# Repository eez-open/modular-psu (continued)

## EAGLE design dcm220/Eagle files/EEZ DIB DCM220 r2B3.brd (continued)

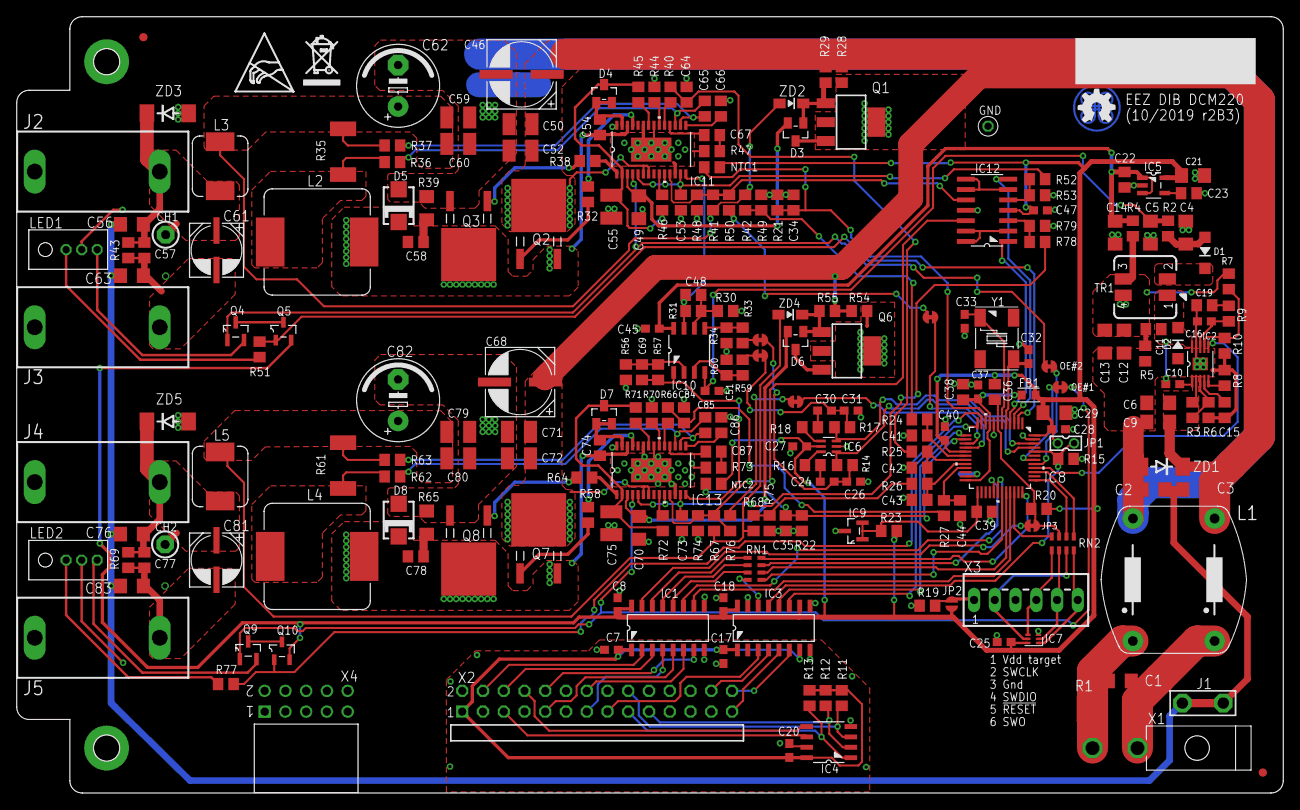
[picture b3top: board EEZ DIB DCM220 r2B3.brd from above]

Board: 2 copper layers, 155.0 x 95.0 mm, 248 parts (1 on the bottom side), 174 nets.

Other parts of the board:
EEZ_SIGNATURE: SIGNATURESMALL; SIGNATURE_5MM
U$2: RECYCLE_BIN1/8
U$4: ESD_SYMBOL

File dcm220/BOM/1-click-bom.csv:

References,Qty,Description,Manufacturer,MPN,Digikey,Mouser,RS,Newark,Farnell
"C1, C2, C3, C56, C63, C76, C83",7,10n/200V,,885342207005,311-4491-1-ND,603C1206KRX7RABB103,CC1206KRX7RABB103,,885342207005
C11,1,330p,,C0805C331J5GACTU,1276-1189-1-ND,80C0805C331J5G,0805N331J500CT,,C0805C331J5GACTU
"C12, C55, C75",3,22u,,MC1206X226M100CT,1276-1287-1-ND,963LMK316ABJ226MLT,LMK316ABJ226KL,,MC1206X226M100CT
"C15, C19, C23, C34, C35, C66, C86",7,10n,,VJ0805Y103JXXPW1BC,490-7194-1-ND,710885012207122,08055C103KAT2A,,VJ0805Y103JXXPW1BC
C16,1,33p,,MC0805N330J500CT,1276-1105-1-ND,C0805C330K5GACTU,C0805C330J5GACTU,,MC0805N330J500CT
"C32, C33",2,4p7,,MC0603N4R7C500CT,311-1740-1-ND,710885012006049,C0603C479C5GACTU,,MC0603N4R7C500CT
C36,1,1n,,VJ0805A102JXACW1BC,732-7858-1-ND,710885012007040,GRM2195C1H102JA01D,,VJ0805A102JXACW1BC
"C38, C53, C57, C73, C77",5,1u,,VJ0805Y105KXXTW1BC,587-1283-1-ND,603CC805MKX7R7BB105,C0805C105K4RACTU,,VJ0805Y105KXXTW1BC
"C39, C41, C42, C43, C44, C67, C87",7,4n7,,GRM2165C1H472JA01D,732-12255-1-ND,810C2012C0G1H472J1,C2012C0G1H472J060AA,,GRM2165C1H472JA01D
"C4, C5, C14, C29, C49, C70",6,4u7,,C3216X7R1E475K160AC,1276-2970-1-ND,963EMK316B7475MLT,C1206C475K3RACTU,,C3216X7R1E475K160AC
"C46, C68",2,EEEFK1H470,,EEEFK1H470P,PCE3815CT-ND,667EEEFK1H470P,EEEFK1H470P,,EEEFK1H470P
"C48, C69",2,100p,,C0805C101JAGACTU,399-15000-1-ND,80C0805C101K5G,CC0805JRNP09BN101,,C0805C101JAGACTU
"C50, C52, C71, C72",4,10u,,GRT31CR61H106KE01L,1276-6736-1-ND,810C3216X7R1HK160AC,UMK316BBJ106KLT,,GRT31CR61H106KE01L
"C54, C74",2,220n,,MC0805B224J250CT,1276-6477-1-ND,963EMK212B7224KGT,UMK212B7224KGT,,MC0805B224J250CT
"C59, C60, C79, C80",6,22u,,MC1210X226K250CT,1276-3373-1-ND,603CC121KKX7R8BB226,CL32A226KAJNNNE,,MC1210X226K250CT
"C6, C9, C21",3,2u2,,C1206C225K5RECTU,1276-2723-1-ND,80C1206C225M5RECLR,UMK316B7225KLHT,,C1206C225K5RECTU
"C61, C81",2,EEEFK1V470P,,EEEFK1V470P,PCE3842CT-ND,667EEEFK1V470P,EEEFK1V470P,,EEEFK1V470P
"C62, C82",2,UVZ1E102MPD,,MCGPR25V108M10X21,93-1305-ND,UVZ1E102MPD1CM,UVZ1E102MPD,,MCGPR25V108M10X21
"C64, C84",2,470p,,MC0805N471J500CT,732-7837-1-ND,710885012007038,0805CG471J9BB,,MC0805N471J500CT
"C65, C85",2,33n,,MC0805B333K250CT,1276-1796-1-ND,710885012207069,08051C333KAT2A,,MC0805B333K250CT
"C7, C8, C10, C17, C18, C20, C24, C26, C27, C28, C30, C31, C37, C40, C45, C47, C51",17,100n,,C0603C104K4RAC7081,490-4774-1-ND,80C0603C104M4R,VJ0603Y104KXJAT,,C0603C104K4RAC7081
"D1, D2, D3, D4, D6, D8, D9, D11",8,SKL16,,RB160MM-60TR,RB160MM-60CT-ND,755RB160MM60TR,RB160MM60TR,,RB160MM60TR
FB1,1,BLM18AG102SH1D,,MMZ1608Y102B,490-7809-1-ND,81BLM18AG102SH1D,BLM18AG102SH1D,,MMZ1608Y102B
IC1,1,Si8662AB-B-IS1,,SI8662AB-B-IS1,SI8662AB-B-IS1-ND,634SI8662ABBIS1,Si8662ABBIS1,,SI8662ABBIS1
IC10,1,MC33272ADR2G,,MC33272ADR2G,MC33272ADR2GOSCT-ND,863MC33272ADR2G,MC33272ADR2G,,MC33272ADR2G
"IC11, IC13",2,LT3763EFE#PBF,,,LT3763EFE#PBF-ND,584LT3763EFE#PBF,,,
IC12,1,MC33274ADR2G,,MC33274ADR2G,MC33274ADR2GOSCT-ND,863MC33274ADR2G,MC33274ADR2G,,MC33274ADR2G
IC2,1,TPS54060DGQ,,TPS54060DGQ .,296-37148-1-ND,595TPS54060DGQR,TPS54060DGQ,,TPS54060DGQ .
IC3,1,Si8641AB-B-IS1,,Si8641AB-B-IS1,SI8641AB-B-IS1-ND,634SI8641ABBIS1,Si8641ABBIS1,,Si8641ABBIS1
IC4,1,M24C32-WMN6P,,M24C32-WMN6P,-,511M24C32WMN6P,M24C32WMN6P,,M24C32WMN6P
IC5,1,LP2985-33DBVR,,LP2985A-33DBVTE4 .,296-18476-1-ND,595LP298533DBVR,LP298533DBVT,,LP2985A33DBVTE4 .
IC6,1,"74HC2G04GW,125",,"74HC2G04GW,125",1727-6045-1-ND,771HC2G04GW125,"74HC2G04GW,125",,"74HC2G04GW,125"
IC8,1,STM32F373C8T6,,STM32F373C8T6,497-13306-ND,511STM32F373C8T6,STM32F373C8T6,,STM32F373C8T6
IC9,1,TL431B,,TL431BCDBZR,296-18866-1-ND,771TL431BIDBZR215,"TL431BIDBZR,215",,TL431BCDBZR
J1,1,4907,,,36-4907-ND,5344907,,,
"J2, J4",2,571-0500,,571-0500-01,-,1646219,5710500,,571050001
"J3, J5",2,571-0100,,571-0100-01,-,1646218,5710100,,571010001
L1,1,RN112-4-02-0M7,,,817-2100-ND,631RN1124020M7,,,
"L2, L4",2,125CDMCCDS-330MC,,7443551331,308-2568-1-ND,851125CDMCCDS330MC,,,7443551331
"L3, L5",2,HPI0630-3R3,,IHLP2020CZER3R3M11,445-180834-1-ND,810VLS6045AF3R3N,,,IHLP2020CZER3R3M11
"LED1, LED2",2,WP42WUM/EGW,,,754-1718-ND,604WP42WUM/EGW,,,
"NTC1, NTC2",2,NTCS0805E3103JMT,,NTCS0805E3103JMT,BC2292CT-ND,594238161553103,NTCS0805E3103JMT,,NTCS0805E3103JMT
"Q1, Q6",2,BSP716NH6327XTSA1,,BSP716NH6327XTSA1,BSP716NH6327XTSA1CT-ND,726BSP716NH6327XTSA,,,BSP716NH6327XTSA1
"Q2, Q3, Q7, Q8",4,NTD5867NLT4G,,NTD5867NLT4G,NTD5867NLT4GOSCT-ND,863NTD5867NLT4G,NTD5867NLT4G,,NTD5867NLT4G
"Q4, Q9",2,BSS205NH6327XTSA1,,BSS205NH6327XTSA1,BSS205NH6327XTSA1CT-ND,BSS205NH6327XTSA1,BSS205NH6327XTSA1,,BSS205NH6327XTSA1
"Q5, Q10",2,BSS84P,,BSS84PH6327XTSA2,BSS84PH6433XTMA1CT-ND,726BSS84PH6327XTSA2,,,BSS84PH6327XTSA2
"R10, R11, R12, R13, R14, R15, R16, R17, R18, R20",10,10K,,RC0805FR-0710KL,311-10.0KCRCT-ND,603RC0805FR0710KL,CRG0805F10K,,RC0805FR0710KL
"R2, R4, R5, R28, R35, R36, R52, R59, R60",9,10R,,MCWR08X10R0FTL,311-10.0CRCT-ND,71CRCW080510R0FKEAC,CRG0805F10R,,MCWR08X10R0FTL
"R21, R22, R41, R48, R65, R72",6,3K3,,MCWR08X3301FTL,A129755CT-ND,,CRG0805F3K3,,MCWR08X3301FTL
"R23, R49, R73",3,120R,,MCWR08X1200FTL,RMCF0805FT120RCT-ND,71CRCW0805120RFKEAC,CRG0805F120R,,MCWR08X1200FTL
"R3, R43, R44, R67, R68",5,47K,,MCWR08X4702FTL,RHM47KKCT-ND,603RC0805FR0747KL,CRCW080547K0FKEA,,MCWR08X4702FTL
"R30, R32, R54, R56",4,20K,,MCWR08X2002FTL,A126349CT-ND,RCG080520K0FKEA,CRCW080520K0FKEA,,MCWR08X2002FTL
"R31, R33, R47, R55, R57, R71",6,12K,,MCWR08X1202FTL,A126337CT-ND,71CRCW080512K0FKEA,CRG0805F12K,,MCWR08X1202FTL
"R34, R58",2,R012/2W,,TLM3AER012JTE,YAG2164CT-ND,279RLP73V3AR012FTDF,TLM3AER012FTE,,TLM3AER012JTE
"R39, R45, R63, R69",4,30K,,ERJ6ENF3002V,P30.0KCCT-ND,603RC0805FR0730KL,,,ERJ6ENF3002V
"R46, R70",2,3K6,,MCWR08X3601FTL,RMCF0805FT3K60CT-ND,603RT0805FRE073K6L,ERJU06F3601V,,MCWR08X3601FTL
"R50, R74",2,11K8,,CRCW080511K8FKEA.,311-11.8KCRCT-ND,603RC0805FR0711K8L,CRCW080511K8FKEA,,CRCW080511K8FKEA.
"R51, R75",2,15K,,WCR0805-15KFI,A126341CT-ND,71CRCW080515K0FKEBC,CRG0805F15K,,WCR080515KFI
"R6, R24, R25, R26, R27, R38, R62",7,2K2,,RC0805FR-072K2L,311-2.20KCRCT-ND,603RC0805FR072K2L,CRCW08052K20FKEA,,RC0805FR072K2L
"R7, R9, R29, R40, R42, R53, R64, R66",8,86K6,,ERJ6ENF8662V,311-86.6KCRCT-ND,603RT0805FRE0786K6L,,,ERJ6ENF8662V
R8,1,330K,,MCWR08X3303FTL,A126361CT-ND,652CR0805FX3303ELF,CRCW0805330KFKEA,,MCWR08X3303FTL
RN1,1,DR1206-33R-4/8,,CAY16-330J4LF,CAY16-330J4LFCT-ND,652CAY16330J4LF,CAY16330J4LF,,CAY16330J4LF
TR1,1,SRF0703-821M,,SRF0703-821M,SRF0703-821MCT-ND,652SRF0703821M,,,SRF0703821M
X1,1,39-30-1020,,39-28-1023,WM3800-ND,53839281023,3928102,,39281023
X2,1,77317-104-28LF,,,S2111EC-14-ND,6497731710428LF,,,
X4,1,DS1024-2*5R0,,613010243121,S9202-ND,710613010243121,613010243121,,613010243121
Y1,1,LF XTAL026392,,LFXTAL026392,1923-1009-ND,449LFXTAL026392BULK,LFXTAL026392,,LFXTAL026392
"ZD1, ZD3, ZD5",3,SMAJ51A,,SMAJ51A,SMAJ51ALFCT-ND,652SMAJ51A,SMAJ51A,,SMAJ51A
"ZD2, ZD4",2,MM3Z9V1T1G,,MM3Z9V1T1G,MM3Z9V1T1GOSCT-ND,863MM3Z9V1T1G,MM3Z9V1T1G,,MM3Z9V1T1G
